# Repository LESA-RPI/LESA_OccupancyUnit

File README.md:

# LESA_OccupancyUnit (BLE_MeshLightingPRFNode)
## Tutorials
https://drive.google.com/drive/folders/18Ncf5kQ7dq59xiIikijq2Gq61cseJHMG?usp=sharing

## Table of Contents
- [Folder Navigation](#folder-navigation)
- [Flow charts](#flow-charts)
- [How to use](#how-to-use)
- [How it works](#how-it-works)
- [How it runs](#how-it-runs)
- [Bluetooth setting](#bluetooth-setting)
- [Tracking Algorithm](#tracking-algorithm)
- [Sensor related files](#sensor-related-files)
- [Summer Team Contact Information](#summer-team-contact-information)

## Folder Navigation
1. [NON-STM32 Project Folder](https://github.com/IAmiku/LESA_OccupancyUnit/tree/main/NON-STM32%20Project%20Folder)
    - [App](https://github.com/IAmiku/LESA_OccupancyUnit/tree/main/NON-STM32%20Project%20Folder/App)
    - [DataBase](https://github.com/IAmiku/LESA_OccupancyUnit/tree/main/NON-STM32%20Project%20Folder/DataBase)
    - [ESP-TCS3430](https://github.com/IAmiku/LESA_OccupancyUnit/tree/main/NON-STM32%20Project%20Folder/ESP-TCS3430)
    - [ESP-TMD3725/readreg](https://github.com/IAmiku/LESA_OccupancyUnit/tree/main/NON-STM32%20Project%20Folder/ESP-TMD3725/readreg)
    - [ESPreceverArduino](https://github.com/IAmiku/LESA_OccupancyUnit/tree/main/NON-STM32%20Project%20Folder/ESPreceverArduino)
2. [STM32CubeIDE](https://github.com/IAmiku/LESA_OccupancyUnit/tree/main/STM32CubeIDE)

Based on STM's *BLE_MeshLightingPRFNode* example, this project gets data from the ToF and color sensor. Bluetooth functionality has not been fully developed

## Flow charts

### Current Program Overview (STM32 occupancy detection)
```mermaid
graph TD
boot(Initilizaiton of STM32 and task registrations) ---> init(Sensor Init) --wait for init to finish--> standby{Standby};
subgraph Appli_mesh.c & others
standby --sw1 short press--> reply1(BLE color value advertisement);
reply1-->standby
standby --sw1 long press--> reply2(BLE ToF value advertisement);
reply2---> standby
standby --sw2 long press--> base(background set up)---> standby
standby -->change{Color INT}-->sensor(wakes up ToF and data pulling)--No blobs present for long period-->standby
standby --sw2 short press--> loopyloop1(ToF matrix to UART)
loopyloop1--sw2 short press--> standby
end
```

### Project Overview 
```mermaid
graph LR
subgraph Room
unit1[Server];unit2[Server];unit3[Server];unit4[Server];unit5{Client};
unit1 & unit2 ---- unit3 & unit4
unit5 ---- unit1
end
unit5 ---- building[Building management sys]
```
Server and Clients are defined by
```
#define ENABLE_SENSOR_MODEL_SERVER                                           (1)
#define ENABLE_SENSOR_MODEL_CLIENT                                           (0)
```
, where server is the one with sensor running, and client is the one requesting or listening

### Conituous ToF matrix pulling configuration
```mermaid
graph TD

server[Server]
esp[EPS32]
server <--HTTP--> esp
subgraph Module
stm[STM32] <--UART--> esp
stm <--I2C--> colorsensor[ColorS]
stm <--I2C--> tof[ToF]
end
```

## Wiring Diagram

Some of external resistors are necessary as the diagram above shown since the L8 TOF board does not internal resistors on it.

## How to use
In order to use this project you must download this entire repository and open the `.project` file in the STM32CubeIDE folder:

|  |  |
|--|--|
| This is how the files should be placed in the workspace folder | Open the project by clicking the .project file |

## How it works

### How it runs

The example software provided by ST uses a sequencer library for scheduling tasks. 

Before using the sequencer it must be initialized by a call to the function :

`UTIL_SEQ_Init( void )`

A function is registered as a task in the sequencer by

`UTIL_SEQ_RegTask( UTIL_SEQ_bm_t TaskId_bm, uint32_t Flags, void (*Task)( void ) )`

The first parameter is the task ID and is a 32-bit value where only one bit should be set, i.e. 
the maximum number of tasks is 32. The second parameter is not used for anything by the library, and the third parameter is a pointer to the function which should be called when it is time for the task to run.

To request a task to be runned, use function 

`UTIL_SEQ_SetTask( UTIL_SEQ_bm_t TaskId_bm , uint32_t Task_Prio )`

Example:
```
UTIL_SEQ_Init( void )
UTIL_SEQ_RegTask((1 << 4), UTIL_SEQ_RFU, my_task_function);
UTIL_SEQ_SetTask((1 << 4), CFG_SEQ_Prio_0);
```

### Bluetooth setting

This project envisioned using BLE mesh to communicate between units. Click [here](Doc/readme.txt) to learn more.

## Tracking Algorithm

[`Tracking_Algo.h`](Core/Inc/Tracking_Algo.h) Function declerations and Macro settings for STM32

[`Tracking_Algo.c`](Core/Src/Tracking_Algo.c) Algorithm itself, can be copied into an online C compiler to run and test

##### TODO: 
- update `void link_latest_frame_to_previous(FIFObuffer *fifobuffer)` to allow multi-frame traceback 
- update `void int find_centers_of_mass(int matrix[N][N], Point *center_of_mass)` in `FrameInfo parse_frame(int matrix[N][N], float deltaX, float deltaY)` to allow track person better

## Sensor related files

##### VL53L8CX (TOF Sensor)

    app_tof.c  ->  /BLE_MeshLightingPRFNode/Application/Core/app_tof.c

    - void MX_TOF_Init(void)
  
      : Initialize the TOF sensor. Validates whether it is properly connected and starts the sensor
  
    - static void MX_VL53L8CX_SimpleRanging_Process(void)
  
      : Read and print out the data if the sensor is properly running
  
    - void MX_TOF_ToggleReso(void)
  
      : A public function that calls toggle_resolution. Change the resolution of TOF sensor
  
    You can change the ranging frequency by modifying "RANGING_FREQUENCY" public variable(Set to 20Hz in the code)

    *custom_ranging_sensor.c  ->  /BLE_MeshLightingPRFNode/Application/Core/custom_ranging_sensor.c

    - int32_t CUSTOM_RANGING_SENSOR_Start(uint32_t Instance, uint8_t Mode)
  
      : Start the TOF sensor
  
    - int32_t CUSTOM_RANGING_SENSOR_Stop(uint32_t Instance)
  
      : Stop the TOF sensor

##### TCS3430 (Tristimulus Sensor)
https://github.com/IAmiku/LESA_OccupancyUnit/tree/main/NON-STM32%20Project%20Folder/ESP-TCS3430

    TCS3430.h  ->  /BLE_MeshLightingPRFNode/Drivers/BSP/TCS3430/TCS3430.h
 
    - Includes all the address of the registers of TCS3430
    
    - Includes Prototype of functions

    - struct tcs3430_optics_val

        : Has X,Y,Z, and IR values

    - struct tcs3430

        reginfo -> data in the registers

        XYZinfo -> Low & High byte of X, Y, Z, and IR1

    TCS3430.c  ->  /BLE_MeshLightingPRFNode/Drivers/BSP/TCS3430/TCS3430.c

    ............

Above two functions are necessary whenever you change the setting of the TOF(such as frequency of configure mode)

Reference:

https://wiki.st.com/stm32mcu/wiki/Connectivity:STM32WB_BLE_MESH_Sensor_Model#/media/File:Connectivity_sensor-demo12.png

### Summer Team Contact Information

•	link10@rpi.edu 

•	kims29@rpi.edu 

•	zhengj8@rpi.edu

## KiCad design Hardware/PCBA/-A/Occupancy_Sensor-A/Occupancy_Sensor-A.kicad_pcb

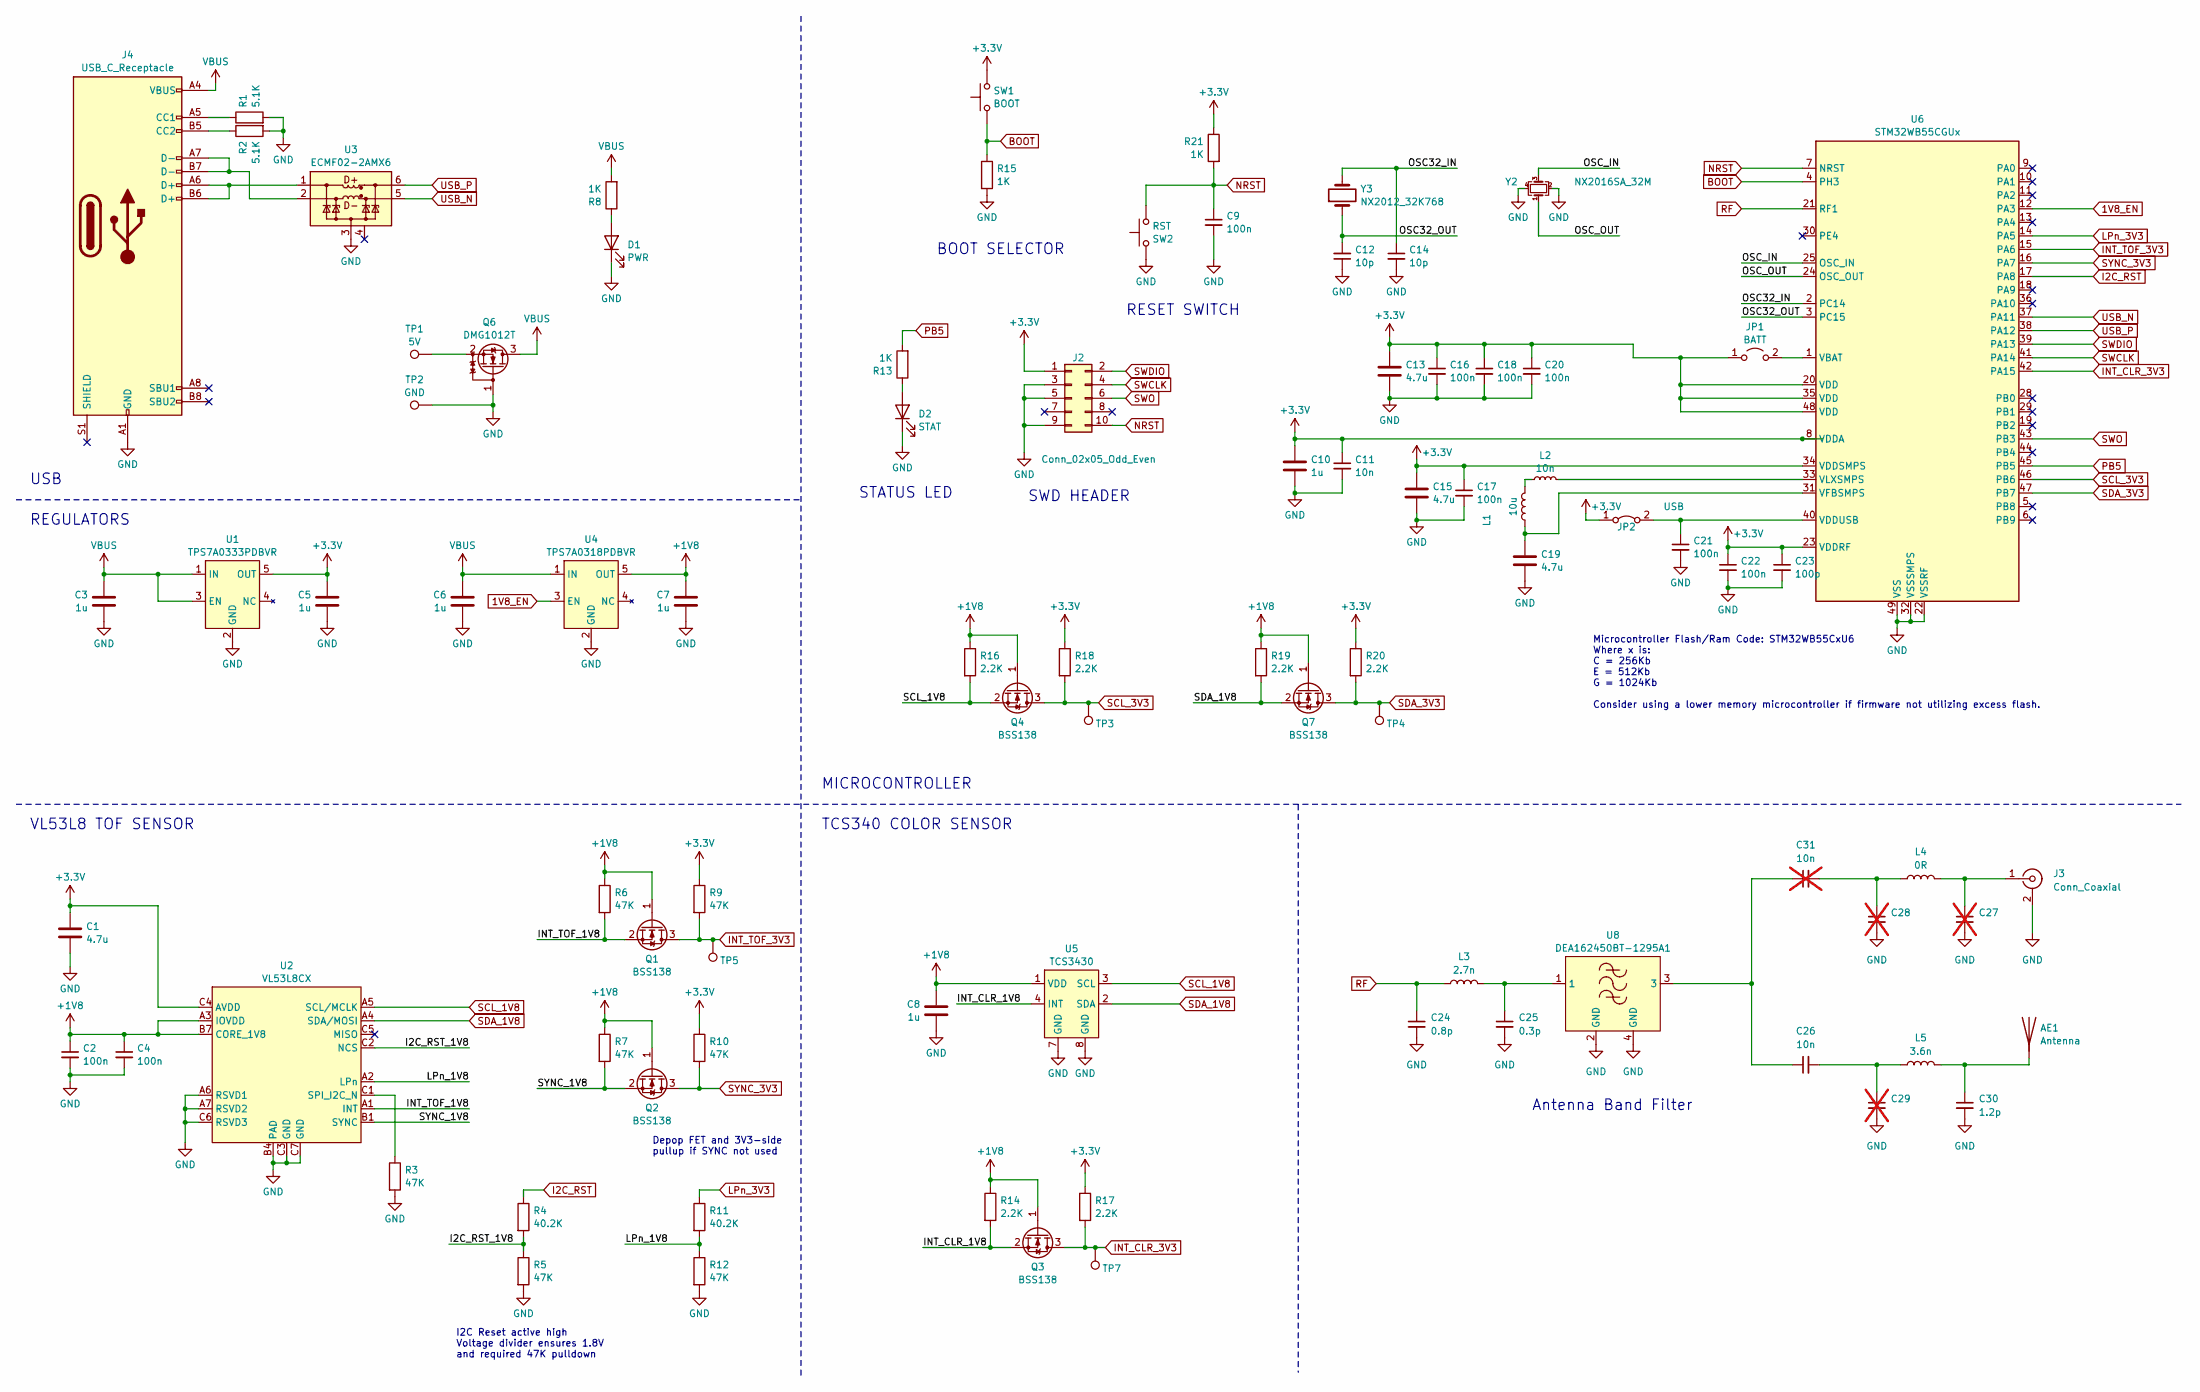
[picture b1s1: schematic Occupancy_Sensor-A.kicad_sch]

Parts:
AE1: Antenna; AN3359_Meander_Antenna
C1, C13, C15, C19: 4.7u; C_0402_1005Metric; Part # CL05A475MP5NRNC
C2, C4, C9, C16, C17, C18, C20, C21, C22: 100n; C_0402_1005Metric; Part # CL05A104KA5NNNC
C3, C5, C6, C7, C8, C10: 1u; C_0402_1005Metric; Part # CL05A105KP5NNNC
C11, C26: 10n; C_0402_1005Metric; Part # CL05B103KB5NNNC
C12, C14: 10p; C_0402_1005Metric; Part # GRM1555C1H100FA01D
C23: 100p; C_0402_1005Metric; Part # GRM1555C1H101JA01D
C24: 0.8p; C_0402_1005Metric; Part # CC0402BRNPO9BNR80
C25: 0.3p; C_0402_1005Metric; Part # GRM1555C1HR30BA01J
C27, C28, C29: C_0402_1005Metric; not fitted
C30: 1.2p; C_0402_1005Metric; Part # CC0402CRNPO9BN1R2
C31: 10n; C_0402_1005Metric; Part # CL05B103KB5NNNC; not fitted
D1: PWR; LED_0603_1608Metric; Part # LTST-C191KRKT
D2: STAT; LED_0603_1608Metric; Part # LTST-C190GKT
J2: Conn_02x05_Odd_Even; PinHeader_2x05_P1.27mm_Vertical_SMD; Part # 20021121-00010C4LF
J3: Conn_Coaxial; CONUFL001-SMD-T; Part # CONUFL001-SMD-T
J4: USB_C_Receptacle; USB4120-03-C; Part # USB4115-03-C
JP1: BATT; SolderJumper-2_P1.3mm_Open_RoundedPad1.0x1.5mm
JP2: USB; SolderJumper-2_P1.3mm_Bridged_RoundedPad1.0x1.5mm
L1: 10u; L_0805_2012Metric; Part # LQM21FN100M70L
L2: 10n; L_0402_1005Metric; Part # LQG15WZ10NJ02D
L3: 2.7n; L_0402_1005Metric; Part # LQG15HS2N7S02D
L4: 0R; R_0603_1608Metric
L5: 3.6n; L_0402_1005Metric; Part # LQG15HS3N6S02
Q1, Q2, Q3, Q4, Q7: BSS138; SOT-23; Part # BSS138
Q6: DMG1012T; SOT-523; Part # DMG1012T-7
R1, R2: 5.1K; R_0402_1005Metric; Part # ERJ-2RKF5101X
R3, R5, R6, R7, R9, R10, R12: 47K; R_0402_1005Metric; Part # ERJ-2RKF4702X
R4, R11: 40.2K; R_0402_1005Metric; Part # RC0402FR-1340K2L
R8, R13, R15, R21: 1K; R_0402_1005Metric; Part # ERJ-2RKF1001X
R14, R16, R17, R18, R19, R20: 2.2K; R_0402_1005Metric; Part # ERJ-2RKF2201X
SW1: BOOT; EVQ-P7A01P; Part # EVQ-P7A01P
SW2: RST; EVQ-P7A01P; Part # EVQ-P7A01P
TP1: 5V; TestPoint_Pad_D2.0mm
TP2: GND; TestPoint_Pad_D2.0mm
TP3: SCL; TestPoint_Pad_D1.0mm
TP4: SDA; TestPoint_Pad_D1.0mm
TP5: INTT; TestPoint_Pad_D1.0mm
TP7: INTC; TestPoint_Pad_D1.0mm
U1: TPS7A0333PDBVR; SOT-23-5; Part # TPS7A0333PDBVR
U2: VL53L8CX; Part # VL53L8CXV0GC/1
U3: ECMF02-2AMX6; ST_UQFN-6L_1.5x1.7mm_P0.5mm; Part # ECMF02-2AMX6
U4: TPS7A0318PDBVR; SOT-23-5; Part # TPS7A0318PDBVR
U5: TCS3430; Part # TCS34303
U6: STM32WB55CGUx; QFN-48-1EP_7x7mm_P0.5mm_EP5.6x5.6mm; Part # STM32WB55CGU6
U8: DEA162450BT-1295A1; Part # DEA162450BT-1295A1
Y2: NX2016SA_32M; Part # CS06465-32M
Y3: NX2012_32K768; Part # MU00797-32.768K

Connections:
1V8_EN: U4.3 (EN), U6.12 (PA3)
+1V8: C2.1, C4.1, C7.1, C8.1, Q1.1 (G), Q2.1 (G), Q3.1 (G), Q4.1 (G), Q7.1 (G), R6.1, R7.1, R14.1, R16.1, R19.1, U2.A3 (IOVDD), U2.B7 (CORE_1V8), U4.5 (OUT), U5.1 (VDD)
+3.3V: C1.1, C5.1, C10.1, C11.1, C13.1, C15.1, C16.1, C17.1, C18.1, C20.1, C22.1, C23.1, J2.1, JP1.1 (A), JP2.1 (A), R9.1, R10.1, R17.1, R18.1, R20.1, R21.1, SW1.2, U1.5 (OUT), U2.C4 (AVDD), U6.8 (VDDA), U6.20 (VDD), U6.23 (VDDRF), U6.34 (VDDSMPS), U6.35 (VDD), U6.48 (VDD)
/I2C_RST_1V8: R4.2, R5.1, U2.C2 (NCS)
/INT_CLR_1V8: Q3.2 (S), R14.2, U5.4 (INT)
/INT_TOF_1V8: Q1.2 (S), R6.2, U2.A1 (INT)
/LPn_1V8: R11.2, R12.1, U2.A2 (LPn)
/OSC32_IN: C14.1, U6.2 (PC14), Y3.2
/OSC32_OUT: C12.2, U6.3 (PC15), Y3.1
/OSC_IN: U6.25 (OSC_IN), Y2.3
/OSC_OUT: U6.24 (OSC_OUT), Y2.1
/SYNC_1V8: Q2.2 (S), R7.2, U2.B1 (SYNC)
BOOT: R15.1, SW1.1, U6.4 (PH3)
GND: C1.2, C2.2, C3.2, C4.2, C5.2, C6.2, C7.2, C8.2, C9.2, C10.2, C11.2, C12.1, C13.2, C14.2, C15.2, C16.2, C17.2, C18.2, C19.2, C20.2, C21.2, C22.2, C23.2, C24.2, C25.2, C27.2, C28.2, C29.2, C30.2, D1.1 (K), D2.1 (K), J2.3, J2.5, J2.9, J3.2 (Ext), J4.A1 (GND), J4.A12 (GND), J4.B1 (GND), J4.B12 (GND), Q6.1 (G), R1.2, R2.2, R3.2, R5.2, R12.2, R15.2, SW2.2, TP2.1, U1.2 (GND), U2.A6 (RSVD1), U2.A7 (RSVD2), U2.B4 (PAD), U2.C3 (GND), U2.C6 (RSVD3), U2.C7 (GND), U3.3 (GND), U4.2 (GND), U5.7 (GND), U5.8 (GND), U6.22 (VSSRF), U6.32 (VSSSMPS), U6.49 (VSS), U8.2 (GND), U8.4 (GND), Y2.2, Y2.4
I2C_RST: R4.1, U6.17 (PA8)
INT_CLR_3V3: Q3.3 (D), R17.2, TP7.1, U6.42 (PA15)
INT_TOF_3V3: Q1.3 (D), R9.2, TP5.1, U6.15 (PA6)
LPn_3V3: R11.1, U6.14 (PA5)
NRST: C9.1, J2.10, R21.2, SW2.1, U6.7 (NRST)
unnamed: AE1.1 (A), C30.1, L5.2
unnamed: C25.1, L3.2, U8.1
unnamed: C26.1, C31.1, U8.3
unnamed: C26.2, C29.1, L5.1
unnamed: C28.1, C31.2, L4.1
unnamed: D1.2 (A), R8.1
unnamed: D2.2 (A), R13.1
unnamed: C27.1, J3.1 (In), L4.2
unnamed: J4.A5 (CC1), R1.1
unnamed: J4.B5 (CC2), R2.1
unnamed: JP1.2 (B), U6.1 (VBAT)
unnamed: C21.1, JP2.2 (B), U6.40 (VDDUSB)
unnamed: L1.2, L2.1
unnamed: Q6.2 (S), TP1.1
unnamed: R3.1, U2.C1 (SPI_I2C_N)
unnamed: J4.A6 (D+), J4.B6 (D+), U3.1 (D+_in)
unnamed: J4.A7 (D-), J4.B7 (D-), U3.2 (D-_in)
unnamed: C19.1, L1.1, U6.31 (VFBSMPS)
unnamed: L2.2, U6.33 (VLXSMPS)
PB5: R13.2, U6.45 (PB5)
RF: C24.1, L3.1, U6.21 (RF1)
SCL_1V8: Q4.2 (S), R16.2, U2.A5 (SCL/MCLK), U5.3 (SCL)
SCL_3V3: Q4.3 (D), R18.2, TP3.1, U6.46 (PB6)
SDA_1V8: Q7.2 (S), R19.2, U2.A4 (SDA/MOSI), U5.2 (SDA)
SDA_3V3: Q7.3 (D), R20.2, TP4.1, U6.47 (PB7)
SWCLK: J2.4, U6.41 (PA14)
SWDIO: J2.2, U6.39 (PA13)
SWO: J2.6, U6.43 (PB3)
SYNC_3V3: Q2.3 (D), R10.2, U6.16 (PA7)
USB_N: U3.5 (D-_out), U6.37 (PA11)
USB_P: U3.6 (D+_out), U6.38 (PA12)
VBUS: C3.1, C6.1, J4.A4 (VBUS), J4.A9 (VBUS), J4.B4 (VBUS), J4.B9 (VBUS), Q6.3 (D), R8.2, U1.1 (IN), U1.3 (EN), U4.1 (IN)

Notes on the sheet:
USB
STATUS LED
TCS340 COLOR SENSOR
Depop FET and 3V3-side pullup if SYNC not used
VL53L8 TOF SENSOR
BOOT SELECTOR
Microcontroller Flash/Ram Code: STM32WB55CxU6 Where x is: C = 256Kb E = 512Kb G = 1024Kb Consider using a lower memory microcontroller if firmware not utilizing excess flash.
REGULATORS
Antenna Band Filter
SWD HEADER
I2C Reset active high Voltage divider ensures 1.8V and required 47K pulldown
RESET SWITCH
MICROCONTROLLER

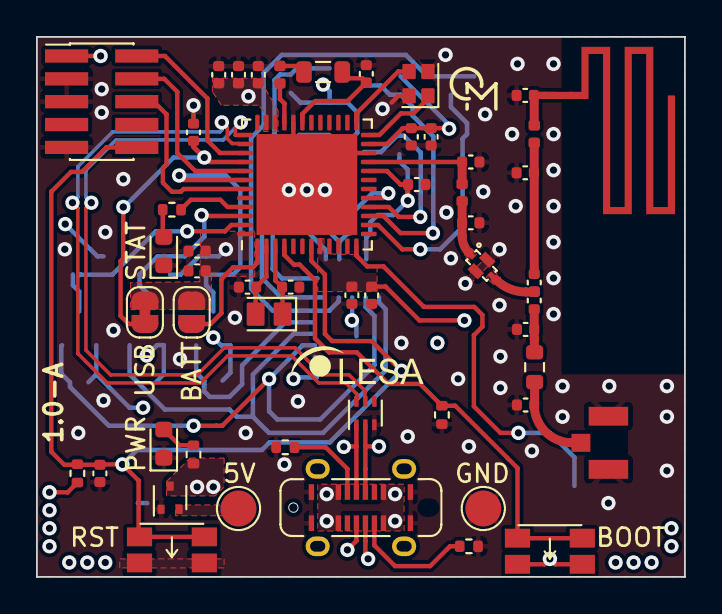
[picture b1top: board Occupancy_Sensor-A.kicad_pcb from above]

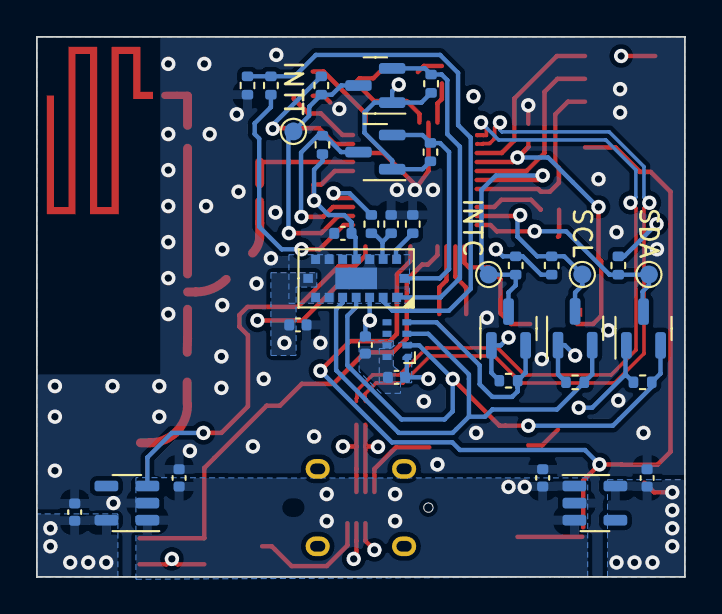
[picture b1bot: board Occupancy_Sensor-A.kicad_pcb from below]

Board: 4 copper layers, 36.0 x 30.0 mm, 88 parts (36 on the bottom side), 51 nets.

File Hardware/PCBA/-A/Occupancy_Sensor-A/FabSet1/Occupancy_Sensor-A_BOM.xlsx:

Designator | Value | Footprint | Digikey Link | Part # | Quantity
C1,C13,C15,C19 | 4.7u | 0402 | https://www.digikey.com/en/products/detail/samsung-electro-m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 | CL05A475MP5NRNC | 4
C2,C4,C9,C16-C18,C20-C22 | 100n | 0402 | https://www.digikey.com/en/products/detail/samsung-electro-m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 | CL05A104KA5NNNC | 9
C3,C5-C8,C10 | 1u | 0402 | https://www.digikey.com/en/products/detail/samsung-electro-m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 | CL05A105KP5NNNC | 6
C11,C26 | 10n | 0402 | https://www.digikey.com/en/products/detail/samsung-electro-m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 | CL05B103KB5NNNC | 2
C12,C14 | 10p | 0402 | https://www.digikey.com/en/products/detail/murata-electronic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 | GRM1555C1H100FA01D | 2
C23 | 100p | 0402 | https://www.digikey.com/en/products/detail/murata-electronic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 | GRM1555C1H101JA01D | 1
C24 | 0.8p | 0402 | https://www.digikey.com/en/products/detail/yageo/CC0402BRNPO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 | CC0402BRNPO9BNR80 | 1
C25 | 0.3p | 0402 | https://www.digikey.com/en/products/detail/murata-electronic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 | GRM1555C1HR30BA01J | 1
C30 | 1.2p | 0402 | https://www.digikey.com/en/products/detail/yageo/CC0402CRNPO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 | CC0402CRNPO9BN1R2 | 1
D1 | PWR | 0603 | https://www.digikey.com/en/products/detail/liteon/LTST-C191K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 | LTST-C191KRKT | 1
D2 | STAT | 0603 | https://www.digikey.com/en/products/detail/liteon/LTST-C190G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 | LTST-C190GKT | 1
J2 | Conn_02x05_Odd_Even | PinHeader_2x05_P1.27mm_Vertical_SMD | https://www.digikey.com/en/products/detail/amphenol-cs-fci/2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 | 20021121-00010C4LF | 1
J3 | Conn_Coaxial | CONUFL001-SMD-T | https://www.digikey.com/en/products/detail/te-connectivity-l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 | CONUFL001-SMD-T | 1
J4 | USB_C_Receptacle | USB4120-03-C | https://www.digikey.com/en/products/detail/gct/USB4115-03-C/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 | USB4115-03-C | 1
L1 | 10u | 0805 | https://www.digikey.com/en/products/detail/murata-electronic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 | LQM21FN100M70L | 1
L2 | 10n | 0402 | https://www.digikey.com/en/products/detail/murata-electronic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 | LQG15WZ10NJ02D | 1
L3 | 2.7n | 0402 | https://www.digikey.com/en/products/detail/murata-electronic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 | LQG15HS2N7S02D | 1
L4 | 0R | 0603 | https://www.digikey.com/en/products/detail/bourns-inc/CR0603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 | CR0603AJ/-000EAS | 1
L5 | 3.6n | 0402 | https://www.digikey.com/en/products/detail/murata-electronic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 | LQG15HS3N6S02 | 1
Q1-Q4,Q7 | BSS138 | SOT-23 | https://www.digikey.com/en/products/detail/onsemi/BSS138/244210 | BSS138 | 5
Q6 | DMG1012T | SOT-523 | https://www.digikey.com/en/products/detail/diodes-incorporat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 | DMG1012T-7 | 1
R1,R2 | 5.1K | 0402 | https://www.digikey.com/en/products/detail/panasonic-electro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 | ERJ-2RKF5101X | 2
R3,R5-R7,R9,R10,R12 | 47K | 0402 | https://www.digikey.com/en/products/detail/panasonic-electro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 | ERJ-2RKF4702X | 7
R4,R11 | 40.2K | 0402 | https://www.digikey.com/en/products/detail/yageo/RC0402FR-13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 | RC0402FR-1340K2L | 2
R8,R13,R15,R21 | 1K | 0402 | https://www.digikey.com/en/products/detail/panasonic-electro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 | ERJ-2RKF1001X | 4
R14,R16-R20 | 2.2K | 0402 | https://www.digikey.com/en/products/detail/panasonic-electro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 | ERJ-2RKF2201X | 6
SW1, SW2 | BOOT, RST | EVQ-P7A01P | https://www.digikey.com/en/products/detail/panasonic-electro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 | EVQ-P7A01P | 2
U1 | TPS7A0333PDBVR | SOT-23-5 | https://www.digikey.com/en/products/detail/texas-instruments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 | TPS7A0333PDBVR | 1
U2 | VL53L8CX | VL53L8CX | https://www.digikey.com/en/products/detail/stmicroelectronic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 | VL53L8CXV0GC/1 | 1
U3 | ECMF02-2AMX6 | ST_UQFN-6L_1.5x1.7mm_P0.5mm | https://www.digikey.com/en/products/detail/stmicroelectronic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 | ECMF02-2AMX6 | 1
U4 | TPS7A0318PDBVR | SOT-23-5 | https://www.digikey.com/en/products/detail/texas-instruments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 | TPS7A0318PDBVR | 1
U5 | TCS3430 | TCS3430 | https://www.digikey.com/en/products/detail/ams-osram-usa-inc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 | TCS34303 | 1
U6 | STM32WB55CGUx | QFN-48-1EP_7x7mm_P0.5mm_EP5.6x5.6mm | https://www.digikey.com/en/products/detail/stmicroelectronic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 | STM32WB55CGU6 | 1
U8 | DEA162450BT-1295A1 | DEA162450BT-1295A1 | https://www.digikey.com/en/products/detail/tdk-corporation/D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 | DEA162450BT-1295A1 | 1
Y2 | NX2016SA_32M | NX2016SA_32M | https://www.digikey.com/en/products/detail/ndk-america-inc/C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 | CS06465-32M | 1
Y3 | NX2012_32K768 | NX2012_32K768 | https://www.digikey.com/en/products/detail/ndk-america-inc/N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 | MU00797-32.768K | 1

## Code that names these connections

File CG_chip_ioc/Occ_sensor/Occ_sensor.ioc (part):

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Mcu.Name=STM32WB55CGUx
Mcu.Package=UFQFPN48
Mcu.UserName=STM32WB55CGUx
PA11.Mode=Device
PA11.Signal=USB_DM
PA12.Mode=Device
PA12.Signal=USB_DP
PA13.Mode=Serial_Wire
PA13.Signal=SYS_JTMS-SWDIO
PA14.Mode=Serial_Wire
PA14.Signal=SYS_JTCK-SWCLK
PA15.GPIOParameters=GPIO_Label,GPIO_ModeDefaultEXTI
PA15.GPIO_Label=INT_CLR
PA15.GPIO_ModeDefaultEXTI=GPIO_MODE_IT_FALLING
PA15.Signal=GPXTI15
PA3.GPIOParameters=PinState,GPIO_Label
PA3.GPIO_Label=LDO_ENABLE
PA3.PinState=GPIO_PIN_SET
PA3.Signal=GPIO_Output
PA5.GPIOParameters=PinState,GPIO_Label
PA5.GPIO_Label=LPn
PA5.PinState=GPIO_PIN_SET
PA5.Signal=GPIO_Output
PA6.GPIOParameters=GPIO_Label,GPIO_ModeDefaultEXTI
PA6.GPIO_Label=INT_TOF
PA6.GPIO_ModeDefaultEXTI=GPIO_MODE_IT_FALLING
PA6.Signal=GPXTI6
PA7.GPIOParameters=PinState,GPIO_PuPd,GPIO_Label
PA7.GPIO_Label=SYNC_TOF
PA7.GPIO_PuPd=GPIO_NOPULL
PA7.PinState=GPIO_PIN_SET
PA7.Signal=GPIO_Output
PA8.GPIOParameters=GPIO_Label
PA8.GPIO_Label=I2C_RST_TOF
PA8.Signal=GPIO_Output
PB5.GPIOParameters=PinState,GPIO_Label
PB5.GPIO_Label=LED
PB5.PinState=GPIO_PIN_RESET
PB5.Signal=GPIO_Output
PB6.Mode=I2C
PB6.Signal=I2C1_SCL
PB7.Mode=I2C
PB7.Signal=I2C1_SDA
PC14-OSC32_IN.Mode=LSE-External-Oscillator
PC14-OSC32_IN.Signal=RCC_OSC32_IN
PC15-OSC32_OUT.Mode=LSE-External-Oscillator
PC15-OSC32_OUT.Signal=RCC_OSC32_OUT
RCC.HSE_VALUE=8000000
RCC.SYSCLKFreq_VALUE=64000000
RCC.SYSCLKSource=RCC_SYSCLKSOURCE_PLLCLK
board=custom

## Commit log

2023-07-21 uploading
2023-07-21 php upload
2023-07-21 move php to server folder
2023-07-25 Create sendToDatabase_Summer.php
    uploaded sendToDatabase_Summer.php
2023-07-25 Update sendToDatabase_Summer.php
    update sendToDatabase_Summer.php
2023-07-25 Update ESPreceverArduino.ino
    added comment
2023-07-26 stm folder
    moved stm files into single folder
2023-07-26 upload server files
    uploaded php, and previous team's code files
2023-07-26 Create LICENSE
2023-07-26 something
2023-07-26 Revert "Update README.md"
    This reverts commit ccada0a1defaa821d08b380ab8f1e69e0d4c3128.
2023-07-26 tryin to roll back
2023-07-26 Revert "Revert "Update README.md""
    This reverts commit 1d9ab2009d01e38c4816ac20cbcfe42ace221691.
2023-07-26 Revert "something"
    This reverts commit b4e7f5f9b6f9bf4c6c6eacfbce0a98130186b99b.
2023-07-26 Revert "tryin to roll back"
    This reverts commit ff0fb536a698a228a44cd208c1b6a2072739ec87.
2023-07-26 Revert "upload server files"
    This reverts commit 683fb0d54f2405ba197ab28d63e856554fe78066.
2023-07-26 Revert "Merge branch 'main' of https://github.com/IAmiku/BLE_MeshLightingPRFNode"
    This reverts commit cc6e01be3f71f41e9e0ab04cfcfdd12129b0051d, reversing
    changes made to 3f9a2da5abd98b4a43d3730e0c2ac256727dd4f4.
2023-07-26 Revert "stm folder"
    This reverts commit 3f9a2da5abd98b4a43d3730e0c2ac256727dd4f4.
2023-07-26 rewind
2023-07-26 linking files
2023-07-26 link files
2023-07-26 remove excessive files
2023-07-26 update server files
    removed old php and uploaded new php files
2023-07-26 Revert me
2023-07-26 Revert "Revert me"
    This reverts commit 12bfeaa48a88817474abb333b8ddf1d4276fc0b0.
2023-07-26 Revert "Merge branch 'main' of https://github.com/IAmiku/LESA_OccupancyUnit"
    This reverts commit 34a891244fd919ee286f9260ac6b7825eea19f3b, reversing
    changes made to 2b86eb3cc53aad48f18b14688456f30d3ee2eb18.
2023-07-26 Revert "update server files"
    This reverts commit 2b86eb3cc53aad48f18b14688456f30d3ee2eb18.
2023-07-26 recovery
2023-07-26 Identify non stm32 project related documents
2023-07-26 restructure
2023-08-08 new functionality
2023-08-08 Update README.md
    Added workspace address
2023-08-08 Update README.md
    Updated workspace direction
2023-08-08 Added
2023-08-08 update php files
2023-08-08 update comments
2023-08-08 Upload App folder
2023-08-08 Changed old to Sage_GUI (old) app
2023-08-08 Removed Occupancy_Integration
2023-08-08 Not important
2023-08-08 removed debug
2023-08-08 update comport
2023-08-10 formatted to use C# reader
2023-08-11 Shrinks the interrupt range
2023-08-14 minor changes
2023-08-14 Create K-Mean Clustering
2023-08-16 Update README.md
    added link to tutorial videos
2023-09-25 Add PCBA KiCad project
2023-10-02 Add 5V-3V3 DCDC, USB, RESET
2023-10-04 Start layout, component fixes
2023-10-04 Add central custom parts directory
2023-10-04 add additional files
2023-10-04 Adding Antenna Design & Band Pass Filter
    Adding LFB182G45CGFD436 into schematic lib
    Adding Antenna Design Schematic Diagram
2023-10-04 General layout, regulator fixes
2023-10-11 Add regulators, TOF, color sensor footprints
2023-10-11 Add kicad-specific gitignore
2023-10-12 Add TOF footprint, component to schematic
2023-10-12 Update antenna circuit
2023-10-16 General layout, footprint fixes
2023-10-18 Layout, power planes, prelim antenna placement
2023-10-18 Create .gitignore
    Add nested gitignore
2023-10-18 Finalize IO pinout, layout
2023-10-20 Layout cleanup, silk fixes
2023-10-22 Adding footprint to the LFB182G45CGFD436
    Adding PCB footprint to the LFB182G45CGFD436
2023-10-23 Add Exclusion Zone Models
    Add rough models with accurate exclusion zones for TCS3430 and VL53L8CX
2023-10-23 Adding coaxial connector
    Adding coaxial connector.
    Remove On board PCB antenna.
2023-11-01 Layout fixes, boot selector, testpoints
2023-11-02 Update exclusion geometries
    Change TCS3430 height to match VL53L8, change each zone to be a different color
2023-11-02 RF layout
2023-11-06 IPEX socket PCB trace change
    Changed the through hole path of the LFB182G45CGFD436 and reroute the PCB trace of the IPEX socket.
2023-11-08 Final TOF sensor layout
2023-11-09 Add Gerbers, PnP, BOM, PDFs for -A rev
2023-12-13 Upload enclosure design files
2024-03-26 Update pin assignment for ToF sensor firmware
2024-04-03 adding the ioc function.
2024-04-16 Adding the ioc file for CG chip
2024-04-16 Complete Pin Assignment for Custom PCB
2024-04-19 Adding BSP driver and some dependent
2024-04-22 Added the Drivers and related files
    Still need works to be done with reroute the I2C init functions. But most of the main files are there.
2024-04-24 actual working version of PCB program
2024-05-15 Complete ToF visualizer
2024-05-30 Updated version of program
2024-05-30 updated version
